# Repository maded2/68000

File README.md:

# 68000
68000 Retro computer (soon with Amiga Chipset)

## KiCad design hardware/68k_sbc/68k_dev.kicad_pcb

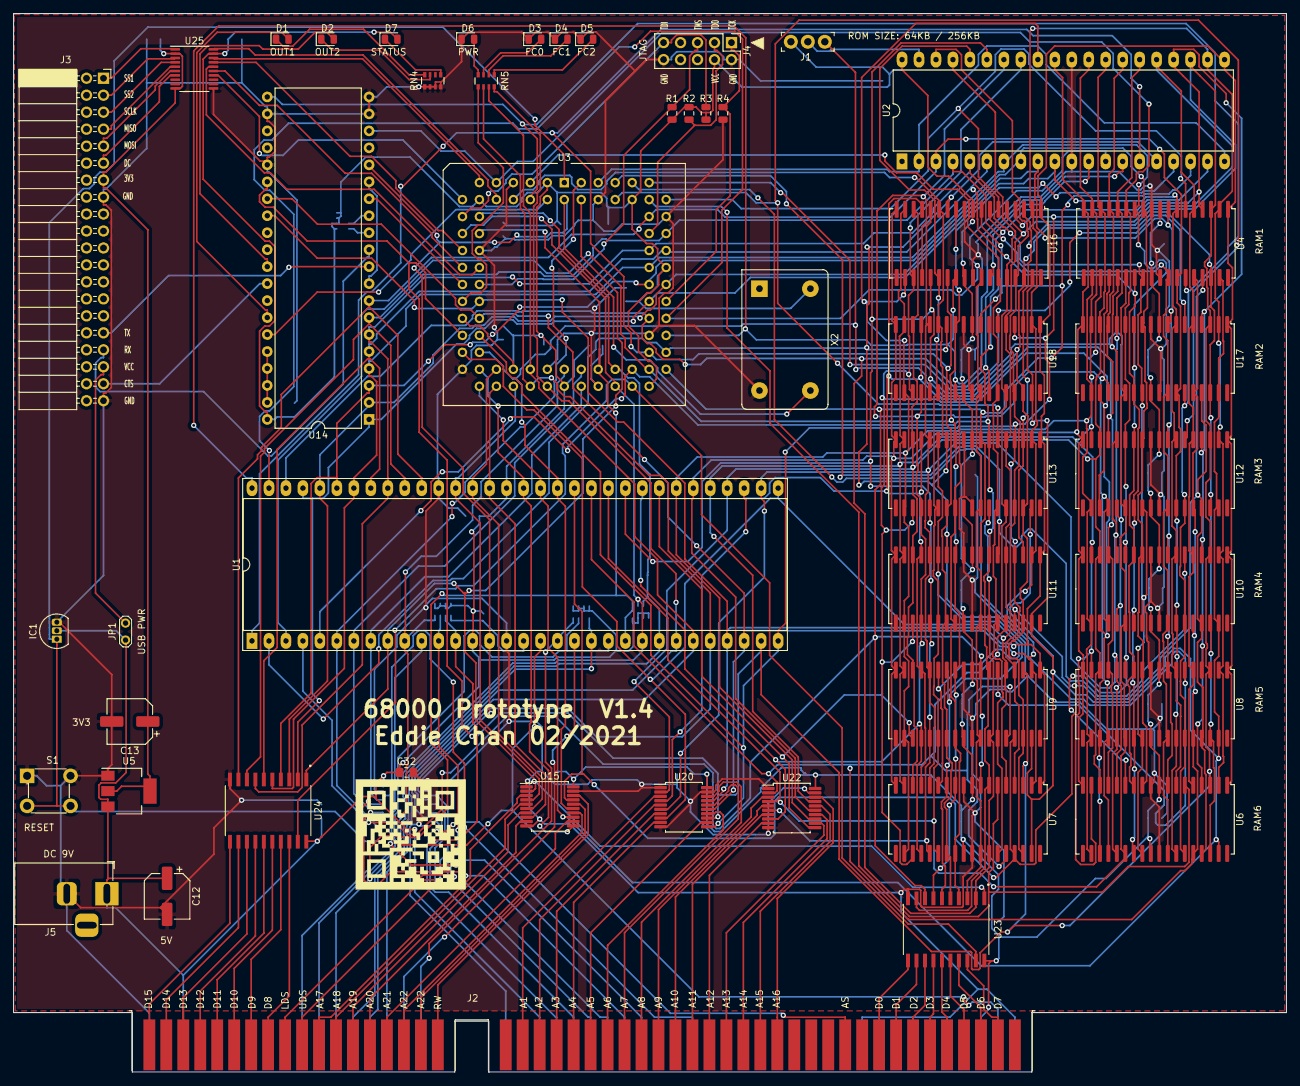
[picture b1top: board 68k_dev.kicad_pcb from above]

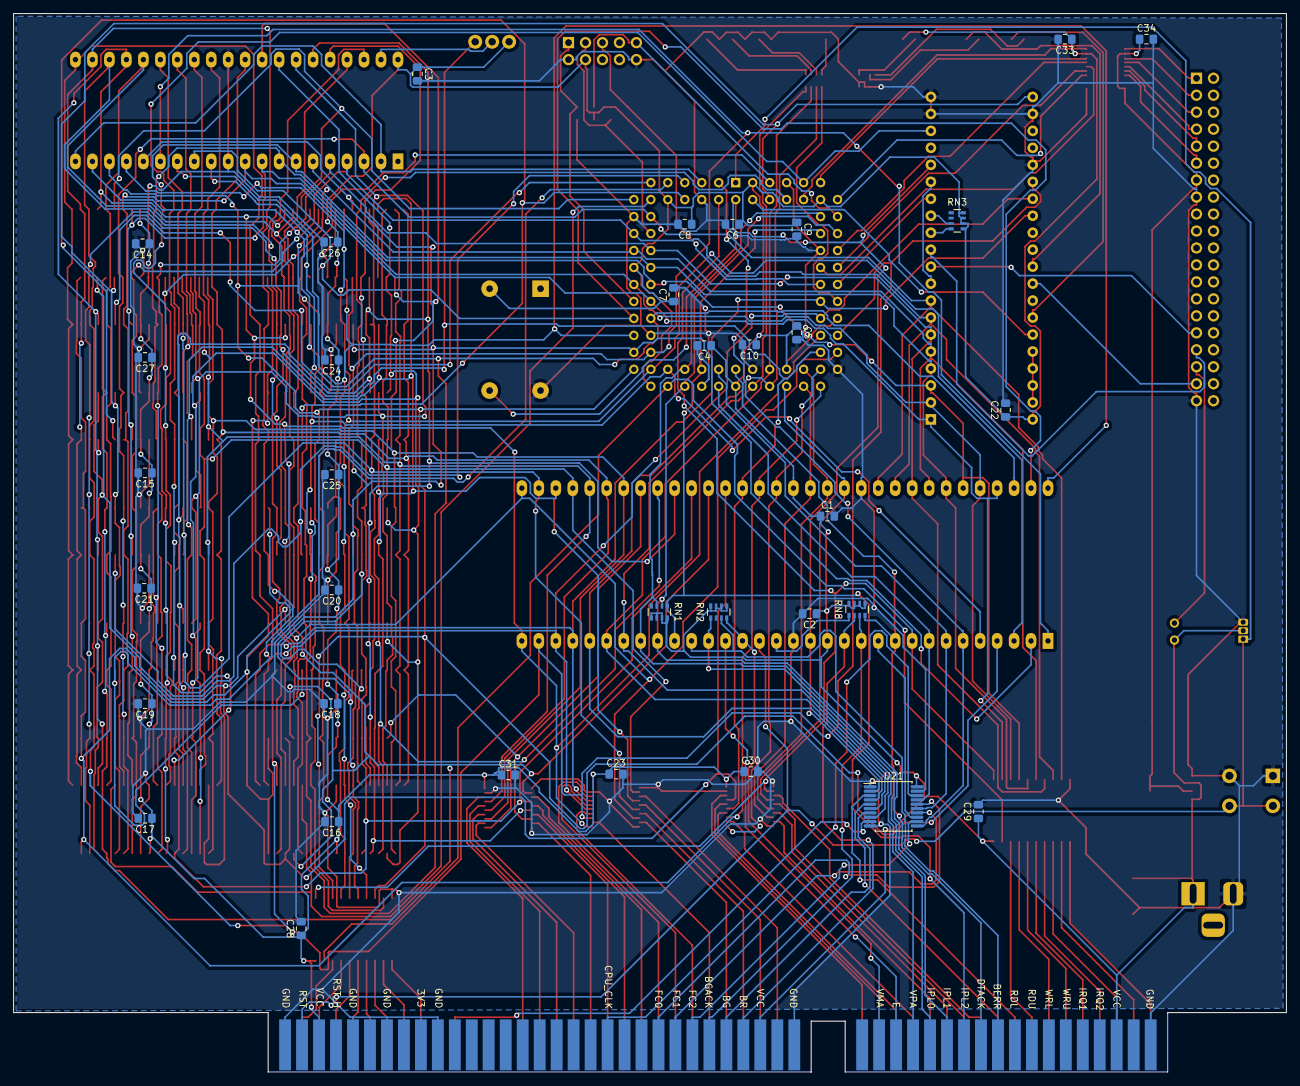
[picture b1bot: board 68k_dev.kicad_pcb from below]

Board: 2 copper layers, 190.5 x 158.4 mm, 83 parts (35 on the bottom side), 160 nets.

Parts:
C1, C2, C3, C7, C8, C9, C10, C14, C15, C16, C17, C18, C19, C20, C21, C22, C23, C24, C25, C26, C27, C28, C29, C30, C31, C32, C33, C34: 100nF; C_0805_2012Metric_Pad1.15x1.40mm_HandSolder
C4, C5, C6: 1uF; C_0805_2012Metric_Pad1.15x1.40mm_HandSolder
C12, C13: 22uF; CP_Elec_6.3x7.7
D1, D2, D3, D4, D5, D6, D7: LED; LED_0805_2012Metric
IC1: DS1813-10+T&R; TO-92L_Inline
J1: 640456-3; PinHeader_1x3_P2.54_Drill1.1mm
J2: Passive_Bus_ISA_16bit; BUS_AT
J3: Conn_02x20_Odd_Even; PinSocket_2x20_P2.54mm_Horizontal
J4: JTAG; PinHeader_2x05_P2.54mm_Vertical
J5: Barrel_Jack; BarrelJack_Horizontal
JP1: Jumper; TestPoint_2Pads_Pitch2.54mm_Drill0.8mm
R1, R2, R3, R4: 1K; R_0805_2012Metric
RN1, RN2, RN4, RN5, RN8: 470; R_Array_Convex_4x0603
RN3: 10K; R_Array_Convex_4x0603
S1: 1825910-6; Switch_Tactile_THT_6x6mm
U1: 68000D; DIP-64_W22.86mm_Socket_LongPads
U2: M27C1024; DIP-40_W15.24mm_LongPads
U3: EPM7128SLC84-15N; PLCC-84_THT-Socket
U4, U6, U7, U8, U9, U10, U11, U12, U13, U16, U17, U18: CY7C1049D; SOJ-36_10.16x23.49mm_P1.27mm_sram
U5: AMS1117-3.3; SOT-223-3_TabPin2
U14: 16550; DIP-40_W15.24mm
U15, U20, U21, U22: 74LS244; SSOP-20_5.3x7.2mm_P0.65mm
U23, U24: SN74LVC245AN; SOIC127P1032X265-20N
U25: TXS0108EPW; TSSOP-20_4.4x6.5mm_P0.65mm
X2: CXO_DIP14; Oscillator_DIP-14_LargePads

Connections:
+3V3: C13.1, C34.1, J3.13, U5.2, U25.2, U25.10
A1: U1.29, U2.21, U3.25, U4.1, U6.1, U7.1, U8.1, U9.1, U10.1, U11.1, U12.1, U13.1, U14.28, U16.1, U17.1, U18.1, U20.17
A2: U1.30, U2.22, U3.27, U4.2, U6.2, U7.2, U8.2, U9.2, U10.2, U11.2, U12.2, U13.2, U14.27, U16.2, U17.2, U18.2, U20.15
A3: U1.31, U2.23, U3.28, U4.3, U6.3, U7.3, U8.3, U9.3, U10.3, U11.3, U12.3, U13.3, U14.26, U16.3, U17.3, U18.3, U20.13
A4: U1.32, U2.24, U3.29, U4.4, U6.4, U7.4, U8.4, U9.4, U10.4, U11.4, U12.4, U13.4, U16.4, U17.4, U18.4, U20.11
A5: U1.33, U2.25, U3.30, U4.5, U6.5, U7.5, U8.5, U9.5, U10.5, U11.5, U12.5, U13.5, U16.5, U17.5, U18.5, U20.8
A6: U1.34, U2.26, U4.14, U6.14, U7.14, U8.14, U9.14, U10.14, U11.14, U12.14, U13.14, U16.14, U17.14, U18.14, U20.6
A7: U1.35, U2.27, U4.15, U6.15, U7.15, U8.15, U9.15, U10.15, U11.15, U12.15, U13.15, U16.15, U17.15, U18.15, U20.4
A8: U1.36, U2.28, U4.16, U6.16, U7.16, U8.16, U9.16, U10.16, U11.16, U12.16, U13.16, U16.16, U17.16, U18.16, U20.2
A9: U1.37, U2.29, U4.17, U6.17, U7.17, U8.17, U9.17, U10.17, U11.17, U12.17, U13.17, U16.17, U17.17, U18.17, U22.17
A10: U1.38, U2.31, U4.18, U6.18, U7.18, U8.18, U9.18, U10.18, U11.18, U12.18, U13.18, U16.18, U17.18, U18.18, U22.15
A11: U1.39, U2.32, U4.20, U6.20, U7.20, U8.20, U9.20, U10.20, U11.20, U12.20, U13.20, U16.20, U17.20, U18.20, U22.13
A12: U1.40, U2.33, U4.21, U6.21, U7.21, U8.21, U9.21, U10.21, U11.21, U12.21, U13.21, U16.21, U17.21, U18.21, U22.11
A13: U1.41, U2.34, U4.22, U6.22, U7.22, U8.22, U9.22, U10.22, U11.22, U12.22, U13.22, U16.22, U17.22, U18.22, U22.8
A14: U1.42, U2.35, U4.23, U6.23, U7.23, U8.23, U9.23, U10.23, U11.23, U12.23, U13.23, U16.23, U17.23, U18.23, U22.6
A15: U1.43, U2.36, U4.24, U6.24, U7.24, U8.24, U9.24, U10.24, U11.24, U12.24, U13.24, U16.24, U17.24, U18.24, U22.4
A16: U1.44, U2.37, U4.32, U6.32, U7.32, U8.32, U9.32, U10.32, U11.32, U12.32, U13.32, U16.32, U17.32, U18.32, U22.2
A17: U1.45, U2.38, U4.33, U6.33, U7.33, U8.33, U9.33, U10.33, U11.33, U12.33, U13.33, U15.17, U16.33, U17.33, U18.33
A18: J1.1, U1.46, U3.31, U4.34, U6.34, U7.34, U8.34, U9.34, U10.34, U11.34, U12.34, U13.34, U15.15, U16.34, U17.34, U18.34
A19: U1.47, U3.33, U4.35, U6.35, U7.35, U8.35, U9.35, U10.35, U11.35, U12.35, U13.35, U15.13, U16.35, U17.35, U18.35
A20: U1.48, U3.34, U15.11
A21: U1.50, U3.35, U15.8
A22: U1.51, U3.36, U15.6
A23: U1.52, U3.37, U15.4
AS: U1.6, U3.83, U21.11
BERR: J2.71, RN2.3, U1.22
BG: U1.11, U21.13
BGACK: J2.26, RN8.3, U1.12
BR: J2.28, RN8.2, U1.13
BUS_A1: J2.61, U20.3
BUS_A2: J2.60, U20.5
BUS_A3: J2.59, U20.7
BUS_A4: J2.58, U20.9
BUS_A5: J2.57, U20.12
BUS_A6: J2.56, U20.14
BUS_A7: J2.55, U20.16
BUS_A8: J2.54, U20.18
BUS_A9: J2.53, U22.3
BUS_A10: J2.52, U22.5
BUS_A11: J2.51, U22.7
BUS_A12: J2.50, U22.9
BUS_A13: J2.49, U22.12
BUS_A14: J2.48, U22.14
BUS_A15: J2.47, U22.16
BUS_A16: J2.46, U22.18
BUS_A17: J2.88, U15.3
BUS_A18: J2.87, U15.5
BUS_A19: J2.86, U15.7
BUS_A20: J2.85, U15.9
BUS_A21: J2.84, U15.12
BUS_A22: J2.83, U15.14
BUS_A23: J2.82, U15.16
BUS_AS: J2.42, U21.9
BUS_BG: J2.27, U21.7
BUS_CPU_CLK: J2.20, U21.18
BUS_D0: J2.40, U23.11
BUS_D1: J2.39, U23.12
BUS_D2: J2.38, U23.13
BUS_D3: J2.37, U23.14
BUS_D4: J2.36, U23.15
BUS_D5: J2.35, U23.16
BUS_D6: J2.34, U23.17
BUS_D7: J2.33, U23.18
BUS_D8: J2.91, U24.18
BUS_D9: J2.92, U24.17
BUS_D10: J2.93, U24.16
BUS_D11: J2.94, U24.15
BUS_D12: J2.95, U24.14
BUS_D13: J2.96, U24.13
BUS_D14: J2.97, U24.12
BUS_D15: J2.98, U24.11
BUS_DIR_CTRL: U3.51, U23.19, U24.19
BUS_FC0: J2.23, U21.16
BUS_FC1: J2.24, U21.14
BUS_FC2: J2.25, U21.12
BUS_LDS: J2.90, U21.3
BUS_RW: J2.81, U15.18
BUS_UDS: J2.89, U21.5
CPU_CLK: U1.15, U3.2, U14.16, U21.2, X2.8
CTS: J3.37, U14.32
D0: U1.5, U2.19, U3.52, U7.7, U9.7, U11.7, U13.7, U16.7, U18.7, U23.9
D1: U1.4, U2.18, U3.54, U7.8, U9.8, U11.8, U13.8, U16.8, U18.8, U23.8
D2: U1.3, U2.17, U3.55, U7.11, U9.11, U11.11, U13.11, U16.11, U18.11, U23.7
D3: U1.2, U2.16, U3.56, U7.12, U9.12, U11.12, U13.12, U16.12, U18.12, U23.6
D4: U1.1, U2.15, U3.57, U7.25, U9.25, U11.25, U13.25, U16.25, U18.25, U23.5
D5: U1.64, U2.14, U3.58, U7.26, U9.26, U11.26, U13.26, U16.26, U18.26, U23.4
D6: U1.63, U2.13, U3.60, U7.29, U9.29, U11.29, U13.29, U16.29, U18.29, U23.3
D7: U1.62, U2.12, U3.61, U7.30, U9.30, U11.30, U13.30, U16.30, U18.30, U23.2
D8: U1.61, U2.10, U3.63, U4.7, U6.7, U8.7, U10.7, U12.7, U14.1, U17.7, U24.2
D9: U1.60, U2.9, U3.64, U4.8, U6.8, U8.8, U10.8, U12.8, U14.2, U17.8, U24.3
D10: U1.59, U2.8, U3.65, U4.11, U6.11, U8.11, U10.11, U12.11, U14.3, U17.11, U24.4
D11: U1.58, U2.7, U3.67, U4.12, U6.12, U8.12, U10.12, U12.12, U14.4, U17.12, U24.5
D12: U1.57, U2.6, U3.68, U4.25, U6.25, U8.25, U10.25, U12.25, U14.5, U17.25, U24.6
D13: U1.56, U2.5, U3.69, U4.26, U6.26, U8.26, U10.26, U12.26, U14.6, U17.26, U24.7
D14: U1.55, U2.4, U3.70, U4.29, U6.29, U8.29, U10.29, U12.29, U14.7, U17.29, U24.8
D15: U1.54, U2.3, U3.73, U4.30, U6.30, U8.30, U10.30, U12.30, U14.8, U17.30, U24.9
DC: U3.12, U25.14
DTACK: J2.70, RN8.4, U1.10, U3.44
E: J2.65, U1.20
FC0: RN5.6, U1.28, U3.39, U21.4
FC1: RN5.7, U1.27, U3.40, U21.6
FC2: RN5.8, U1.26, U3.41, U21.8
GND: C1.2, C2.2, C3.2, C4.2, C5.2, C6.2, C7.2, C8.2, C9.2, C10.2, C12.2, C13.2, C14.2, C15.2, C16.2, C17.2, C18.2, C19.2, C20.2, C21.2, C22.2, C23.2, C24.2, C25.2, C26.2, C27.2, C28.2, C29.2, C30.2, C31.2, C32.2, C33.2, C34.2, D3.1, D4.1, D5.1, D6.1, IC1.3, J2.1, J2.5, J2.7, J2.10, J2.31, J2.80, J3.15, J3.39, J4.2, J4.10, J5.2, R4.2, RN4.1, RN4.2, RN4.3, RN4.4, S1.1, S1.2, U1.16, U1.53, U2.11, U2.30, U3.7, U3.19, U3.32, U3.42, U3.47, U3.59, U3.72, U3.82, U4.10, U4.28, U5.1, U6.10, U6.28, U7.10, U7.28, U8.10, U8.28, U9.10, U9.28, U10.10, U10.28, U11.10, U11.28, U12.10, U12.28, U13.10, U13.28, U14.19, U14.20, U14.22, U14.25, U15.1, U15.10, U15.19, U16.10, U16.28, U17.10, U17.28, U18.10, U18.28, U20.1, U20.10, U20.19, U21.1, U21.10, U21.19, U22.1, U22.10, U22.19, U23.10, U24.10, U25.11, X2.7
IO_SEL1: U3.22, U14.14
IPL0: J2.67, RN1.3, U1.25, U3.15, U3.50
IPL1: J2.68, RN1.2, U1.24, U3.16, U3.49
IPL2: J2.69, RN1.1, U1.23, U3.17, U3.48
LDS: U1.8, U3.45, U21.17
MISO: U3.21, U25.16
MOSI: U3.20, U25.15
unnamed: D1.1, RN4.8
unnamed: D1.2, U14.34
unnamed: D2.1, RN4.7
unnamed: D2.2, U14.31
unnamed: D3.2, RN5.3
unnamed: D4.2, RN5.2
unnamed: D5.2, RN5.1
unnamed: D6.2, RN5.4
unnamed: D7.1, RN4.5
unnamed: J1.2, U2.39
unnamed: J3.1, U25.1
unnamed: J3.3, U25.3
unnamed: J3.5, U25.4
unnamed: J3.7, U25.5
unnamed: J3.9, U25.6
unnamed: J3.11, U25.7
unnamed: J3.35, JP1.2
unnamed: RN3.3, U14.13
unnamed: RN3.4, U14.12
unnamed: RN8.1, U1.17
unnamed: U14.9, U14.15
unnamed: U14.36, U14.37, U14.38, U14.39
RAM1_SEL: U3.76, U6.6, U7.6
RAM2_SEL: U3.77, U8.6, U9.6
RAM3_SEL: U3.79, U10.6, U11.6
RAM4_SEL: U3.80, U12.6, U13.6
RAM5_SEL: U3.74, U4.6, U16.6
RAM6_SEL: U3.75, U17.6, U18.6
RDL: U3.5, U7.31, U9.31, U11.31, U13.31, U16.31, U18.31
RDU: U3.6, U4.31, U6.31, U8.31, U10.31, U12.31, U14.21, U17.31
ROM_SEL: U2.2, U2.20, U3.81
RST: IC1.1, J2.2, S1.3, S1.4, U1.18, U3.1
RST_H: U3.4, U14.35
RW: U1.9, U3.84, U15.2, U23.1, U24.1
RX: J3.33, U14.11
SCLK: U3.18, U25.17
SS1: U3.10, U25.20
SS2: U3.11, U25.18
STATUS: RN5.5, U3.24
TCK: J4.1, R4.1, U3.62
TDI: J4.9, R3.2, U3.14
TDO: J4.3, R2.2, U3.71
TMS: J4.5, R1.2, U3.23
TX: J3.31, U14.10
UDS: U1.7, U3.46, U21.15
VCC: C1.1, C2.1, C3.1, C4.1, C5.1, C6.1, C7.1, C8.1, C9.1, C10.1, C12.1, C14.1, C15.1, C16.1, C17.1, C18.1, C19.1, C20.1, C21.1, C22.1, C23.1, C24.1, C25.1, C26.1, C27.1, C28.1, C29.1, C30.1, C31.1, C32.1, C33.1, D7.2, IC1.2, J1.3, J2.3, J2.29, J2.78, J4.4, J5.1, JP1.1, R1.1, R2.1, R3.1, RN1.5, RN1.6, RN1.7, RN1.8, RN2.5, RN2.6, RN2.7, RN2.8, RN3.5, RN3.6, RN3.7, RN3.8, RN8.5, RN8.6, RN8.7, RN8.8, U1.14, U1.49, U2.40, U3.3, U3.13, U3.26, U3.38, U3.43, U3.53, U3.66, U3.78, U4.9, U4.27, U5.3, U6.9, U6.27, U7.9, U7.27, U8.9, U8.27, U9.9, U9.27, U10.9, U10.27, U11.9, U11.27, U12.9, U12.27, U13.9, U13.27, U14.40, U15.20, U16.9, U16.27, U17.9, U17.27, U18.9, U18.27, U20.20, U21.20, U22.20, U23.20, U24.20, U25.19, X2.14
VMA: J2.64, RN2.4, U1.19
VPA: J2.66, RN2.1, U1.21
WRL: U3.8, U7.13, U9.13, U11.13, U13.13, U16.13, U18.13
WRU: U3.9, U4.13, U6.13, U8.13, U10.13, U12.13, U14.18, U17.13

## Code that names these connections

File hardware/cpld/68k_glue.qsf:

# -------------------------------------------------------------------------- #
#
# Copyright (C) 1991-2013 Altera Corporation
# Your use of Altera Corporation's design tools, logic functions 
# and other software and tools, and its AMPP partner logic 
# functions, and any output files from any of the foregoing 
# (including device programming or simulation files), and any 
# associated documentation or information are expressly subject 
# to the terms and conditions of the Altera Program License 
# Subscription Agreement, Altera MegaCore Function License 
# Agreement, or other applicable license agreement, including, 
# without limitation, that your use is for the sole purpose of 
# programming logic devices manufactured by Altera and sold by 
# Altera or its authorized distributors.  Please refer to the 
# applicable agreement for further details.
#
# -------------------------------------------------------------------------- #
#
# Quartus II 64-Bit
# Version 13.0.1 Build 232 06/12/2013 Service Pack 1 SJ Web Edition
# Date created = 21:42:39  November 19, 2020
#
# -------------------------------------------------------------------------- #
#
# Notes:
#
# 1) The default values for assignments are stored in the file:
#		68k_glue_assignment_defaults.qdf
#    If this file doesn't exist, see file:
#		assignment_defaults.qdf
#
# 2) Altera recommends that you do not modify this file. This
#    file is updated automatically by the Quartus II software
#    and any changes you make may be lost or overwritten.
#
# -------------------------------------------------------------------------- #


set_global_assignment -name FAMILY MAX7000S
set_global_assignment -name DEVICE "EPM7128SLC84-15"
set_global_assignment -name TOP_LEVEL_ENTITY glue
set_global_assignment -name ORIGINAL_QUARTUS_VERSION "13.0 SP1"
set_global_assignment -name PROJECT_CREATION_TIME_DATE "21:42:39  NOVEMBER 19, 2020"
set_global_assignment -name LAST_QUARTUS_VERSION "13.0 SP1"
set_global_assignment -name PROJECT_OUTPUT_DIRECTORY output_files
set_global_assignment -name DEVICE_FILTER_PACKAGE PLCC
set_global_assignment -name DEVICE_FILTER_PIN_COUNT 84
set_global_assignment -name DEVICE_FILTER_SPEED_GRADE 15
set_global_assignment -name ERROR_CHECK_FREQUENCY_DIVISOR "-1"
set_global_assignment -name EDA_SIMULATION_TOOL "ModelSim-Altera (Verilog)"
set_global_assignment -name EDA_OUTPUT_DATA_FORMAT "VERILOG HDL" -section_id eda_simulation
set_global_assignment -name VERILOG_FILE 68k_glue.v
set_global_assignment -name OPTIMIZE_HOLD_TIMING OFF
set_global_assignment -name OPTIMIZE_MULTI_CORNER_TIMING OFF
set_global_assignment -name FITTER_EFFORT "STANDARD FIT"
set_global_assignment -name MAX7000_DEVICE_IO_STANDARD TTL
set_location_assignment PIN_2 -to clk
set_location_assignment PIN_83 -to as
set_location_assignment PIN_25 -to addr[1]
set_location_assignment PIN_27 -to addr[2]
set_location_assignment PIN_28 -to addr[3]
set_location_assignment PIN_29 -to addr[4]
set_location_assignment PIN_30 -to addr[5]
set_location_assignment PIN_31 -to addr[6]
set_location_assignment PIN_33 -to addr[7]
set_location_assignment PIN_34 -to addr[8]
set_location_assignment PIN_35 -to addr[9]
set_location_assignment PIN_36 -to addr[10]
set_location_assignment PIN_37 -to addr[11]
set_location_assignment PIN_48 -to addr[12]
set_location_assignment PIN_49 -to addr[13]
set_location_assignment PIN_50 -to addr[14]
set_location_assignment PIN_51 -to addr[15]
set_location_assignment PIN_52 -to addr[16]
set_location_assignment PIN_54 -to addr[17]
set_location_assignment PIN_55 -to addr[18]
set_location_assignment PIN_56 -to addr[19]
set_location_assignment PIN_57 -to addr[20]
set_location_assignment PIN_58 -to addr[21]
set_location_assignment PIN_60 -to addr[22]
set_location_assignment PIN_61 -to addr[23]
set_location_assignment PIN_45 -to lds
set_location_assignment PIN_46 -to uds
set_location_assignment PIN_5 -to rdl
set_location_assignment PIN_6 -to rdu
set_location_assignment PIN_8 -to wrl
set_location_assignment PIN_9 -to wru
set_location_assignment PIN_63 -to data[0]
set_location_assignment PIN_64 -to data[1]
set_location_assignment PIN_65 -to data[2]
set_location_assignment PIN_67 -to data[3]
set_location_assignment PIN_68 -to data[4]
set_location_assignment PIN_69 -to data[5]
set_location_assignment PIN_70 -to data[6]
set_location_assignment PIN_73 -to data[7]
set_location_assignment PIN_81 -to rom_sel
set_location_assignment PIN_80 -to ram4_sel
set_location_assignment PIN_79 -to ram3_sel
set_location_assignment PIN_77 -to ram2_sel
set_location_assignment PIN_76 -to ram1_sel
set_location_assignment PIN_75 -to io2_sel
set_location_assignment PIN_74 -to io1_sel
set_location_assignment PIN_39 -to fc[0]
set_location_assignment PIN_40 -to fc[1]
set_location_assignment PIN_41 -to fc[2]
set_location_assignment PIN_44 -to dtack
set_location_assignment PIN_71 -to TDO
set_location_assignment PIN_14 -to TDI
set_location_assignment PIN_62 -to TCK
set_location_assignment PIN_23 -to TMS
set_location_assignment PIN_1 -to rst
set_location_assignment PIN_4 -to rst_h
set_location_assignment PIN_84 -to rw
set_location_assignment PIN_15 -to ipl[0]
set_location_assignment PIN_16 -to ipl[1]
set_location_assignment PIN_17 -to ipl[2]
set_location_assignment PIN_22 -to irq1
set_location_assignment PIN_24 -to irq2
set_location_assignment PIN_18 -to sclk
set_location_assignment PIN_20 -to mosi
set_location_assignment PIN_21 -to miso
set_location_assignment PIN_10 -to ss1
set_location_assignment PIN_11 -to ss2
set_instance_assignment -name GLOBAL_SIGNAL GLOBAL_CLOCK -to clk
set_instance_assignment -name GLOBAL_SIGNAL "GLOBAL CLOCK" -to as
set_instance_assignment -name GLOBAL_SIGNAL OFF -to rst
set_instance_assignment -name GLOBAL_SIGNAL OFF -to rw
set_location_assignment PIN_12 -to dc
set_global_assignment -name VERILOG_FILE SPI_Master.v
set_instance_assignment -name FAST_INPUT_REGISTER ON -to as
set_instance_assignment -name FAST_INPUT_REGISTER ON -to clk
set_global_assignment -name MAX7000_OPTIMIZATION_TECHNIQUE AREA
set_global_assignment -name SYNTH_TIMING_DRIVEN_SYNTHESIS OFF
set_global_assignment -name SIGNALTAP_FILE stp1.stp

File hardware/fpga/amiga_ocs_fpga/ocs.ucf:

//global system clock
NET "sys_clk" LOC = A10 | IOSTANDARD = LVTTL;
//reset signal
NET "rst" 	LOC = T8 	| IOSTANDARD = LVTTL;
//led_1 signal
NET "led_1" LOC = T9 | IOSTANDARD = LVTTL;
//led_2 signal
NET "led_2" LOC = R9 | IOSTANDARD = LVTTL;

// U8
#NET "data<0>"      LOC = A14   | IOSTANDARD = LVTTL;
#NET "data<1>"      LOC = C13   | IOSTANDARD = LVTTL;
#NET "data<2>"      LOC = B12   | IOSTANDARD = LVTTL;
#NET "data<3>"      LOC = C11   | IOSTANDARD = LVTTL;
#NET "data<4>"      LOC = B10   | IOSTANDARD = LVTTL;
#NET "data<5>"      LOC = C9    | IOSTANDARD = LVTTL;
#NET "data<6>"      LOC = B8    | IOSTANDARD = LVTTL;
#NET "data<7>"      LOC = C7    | IOSTANDARD = LVTTL;
#NET "data<8>"      LOC = B6    | IOSTANDARD = LVTTL;
#NET "data<9>"      LOC = B5    | IOSTANDARD = LVTTL;
#NET "data<10>"     LOC = E10   | IOSTANDARD = LVTTL;
#NET "data<11>"     LOC = E11   | IOSTANDARD = LVTTL;
#NET "data<12>"     LOC = F9    | IOSTANDARD = LVTTL;
#NET "data<13>"     LOC = C8    | IOSTANDARD = LVTTL;
#NET "data<14>"     LOC = E7    | IOSTANDARD = LVTTL;
#NET "data<15>"     LOC = F7    | IOSTANDARD = LVTTL;
#NET "rw"        LOC = D6    | IOSTANDARD = LVTTL;
NET "cpu_clk"   LOC = M7    | IOSTANDARD = LVTTL;
#NET "rst"       LOC = N8    | IOSTANDARD = LVTTL;
#NET "lds"       LOC = P9    | IOSTANDARD = LVTTL;
#NET "uds"       LOC = T5    | IOSTANDARD = LVTTL;
#NET "dtack"     LOC = T6    | IOSTANDARD = LVTTL;3
#NET "bgack"     LOC = N9    | IOSTANDARD = LVTTL;
#NET "vma"       LOC = L8    | IOSTANDARD = LVTTL;
#NET "e"         LOC = L10   | IOSTANDARD = LVTTL;
#NET "vpa"       LOC = P12   | IOSTANDARD = LVTTL;
#NET "berr"      LOC = R9    | IOSTANDARD = LVTTL;

#NET "addr<1>"      LOC = B14   | IOSTANDARD = LVTTL;
#NET "addr<2>"      LOC = A13   | IOSTANDARD = LVTTL;
#NET "addr<3>"      LOC = A12   | IOSTANDARD = LVTTL;
#NET "addr<4>"      LOC = A11   | IOSTANDARD = LVTTL;
#NET "addr<5>"      LOC = A9    | IOSTANDARD = LVTTL;
#NET "addr<6>"      LOC = A8    | IOSTANDARD = LVTTL;
#NET "addr<7>"      LOC = A7    | IOSTANDARD = LVTTL;
#NET "addr<8>"      LOC = A6    | IOSTANDARD = LVTTL;
#NET "addr<9>"      LOC = A5    | IOSTANDARD = LVTTL;
#NET "addr<10>"     LOC = A4    | IOSTANDARD = LVTTL;
#NET "addr<11>"     LOC = C10   | IOSTANDARD = LVTTL;
#NET "addr<12>"     LOC = F10   | IOSTANDARD = LVTTL;
#NET "addr<13>"     LOC = D9    | IOSTANDARD = LVTTL;
#NET "addr<14>"     LOC = D8    | IOSTANDARD = LVTTL;
#NET "addr<15>"     LOC = E6    | IOSTANDARD = LVTTL;
#NET "addr<16>"     LOC = C6    | IOSTANDARD = LVTTL;
#NET "addr<17>"     LOC = N6    | IOSTANDARD = LVTTL;
#NET "addr<18>"     LOC = P6    | IOSTANDARD = LVTTL;
#NET "addr<19>"     LOC = L7    | IOSTANDARD = LVTTL;
#NET "addr<20>"     LOC = T4    | IOSTANDARD = LVTTL;
#NET "addr<21>"     LOC = R5    | IOSTANDARD = LVTTL;
#NET "addr<22>"     LOC = T7    | IOSTANDARD = LVTTL;
#NET "addr<23>"     LOC = M9    | IOSTANDARD = LVTTL;
NET "as"        LOC = M10   | IOSTANDARD = LVTTL;
#NET "ipl<0>"    LOC = P11   | IOSTANDARD = LVTTL;
#NET "ipl<1>"    LOC = M11   | IOSTANDARD = LVTTL;
#NET "ipl<2>"    LOC = T9    | IOSTANDARD = LVTTL;



// U7
NET "vga_vsync"    LOC = C15   | IOSTANDARD = LVTTL;
NET "vga_hsync"    LOC = D14   | IOSTANDARD = LVTTL;

NET "vga_b<0>" LOC = E15  | IOSTANDARD = LVTTL;
NET "vga_b<1>" LOC = F15  | IOSTANDARD = LVTTL;
NET "vga_b<2>" LOC = G11  | IOSTANDARD = LVTTL;
NET "vga_b<3>" LOC = F14  | IOSTANDARD = LVTTL;
NET "vga_b<4>" LOC = G16  | IOSTANDARD = LVTTL;
NET "vga_b<5>" LOC = H15  | IOSTANDARD = LVTTL;

NET "vga_g<0>" LOC = G12  | IOSTANDARD = LVTTL;
NET "vga_g<1>" LOC = H13  | IOSTANDARD = LVTTL;
NET "vga_g<2>" LOC = J14  | IOSTANDARD = LVTTL;
NET "vga_g<3>" LOC = J11  | IOSTANDARD = LVTTL;
NET "vga_g<4>" LOC = K14  | IOSTANDARD = LVTTL;
NET "vga_g<5>" LOC = K15  | IOSTANDARD = LVTTL;

NET "vga_r<0>" LOC = L16  | IOSTANDARD = LVTTL;
NET "vga_r<1>" LOC = K11  | IOSTANDARD = LVTTL;
NET "vga_r<2>" LOC = M15  | IOSTANDARD = LVTTL;
NET "vga_r<3>" LOC = N14  | IOSTANDARD = LVTTL;
NET "vga_r<4>" LOC = M13  | IOSTANDARD = LVTTL;
NET "vga_r<5>" LOC = L12  | IOSTANDARD = LVTTL;

#NET "gpio00"    LOC = E12   | IOSTANDARD = LVTTL;
#NET "gpio01"    LOC = B15   | IOSTANDARD = LVTTL;
#NET "gpio02"    LOC = C15   | IOSTANDARD = LVTTL;
#NET "gpio03"    LOC = D14   | IOSTANDARD = LVTTL;
#NET "gpio04"    LOC = E15   | IOSTANDARD = LVTTL;
#NET "gpio05"    LOC = F15   | IOSTANDARD = LVTTL;
#NET "gpio06"    LOC = G11   | IOSTANDARD = LVTTL;
#NET "gpio07"    LOC = F14   | IOSTANDARD = LVTTL;
#NET "gpio08"    LOC = G16   | IOSTANDARD = LVTTL;
#NET "gpio09"    LOC = H15   | IOSTANDARD = LVTTL;
#NET "gpio10"    LOC = G12   | IOSTANDARD = LVTTL;
#NET "gpio11"    LOC = H13   | IOSTANDARD = LVTTL;
#NET "gpio12"    LOC = J14   | IOSTANDARD = LVTTL;
#NET "gpio13"    LOC = J11   | IOSTANDARD = LVTTL;
#NET "gpio14"    LOC = K14   | IOSTANDARD = LVTTL;
#NET "gpio15"    LOC = K15   | IOSTANDARD = LVTTL;
#NET "gpio16"    LOC = L16   | IOSTANDARD = LVTTL;
#NET "gpio17"    LOC = K11   | IOSTANDARD = LVTTL;
#NET "gpio18"    LOC = M15   | IOSTANDARD = LVTTL;
#NET "gpio19"    LOC = N14   | IOSTANDARD = LVTTL;
#NET "gpio20"    LOC = M13   | IOSTANDARD = LVTTL;
#NET "gpio21"    LOC = L12   | IOSTANDARD = LVTTL;
#NET "gpio26"    LOC = P15   | IOSTANDARD = LVTTL;
#NET "gpio27"    LOC = R15   | IOSTANDARD = LVTTL;
#NET "gpio24"    LOC = R14   | IOSTANDARD = LVTTL;
#NET "gpio23"    LOC = T13   | IOSTANDARD = LVTTL;
#NET "gpio22"    LOC = T12   | IOSTANDARD = LVTTL;
#
#NET "gpio37"    LOC = E13   | IOSTANDARD = LVTTL;
#NET "gpio36"    LOC = B16   | IOSTANDARD = LVTTL;
#NET "gpio35"    LOC = C16   | IOSTANDARD = LVTTL;
#NET "gpio34"    LOC = D16   | IOSTANDARD = LVTTL;
#NET "gpio33"    LOC = E16   | IOSTANDARD = LVTTL;
#NET "gpio32"    LOC = F16   | IOSTANDARD = LVTTL;
#NET "gpio31"    LOC = F12   | IOSTANDARD = LVTTL;
#NET "gpio30"    LOC = F13   | IOSTANDARD = LVTTL;
#NET "gpio29"    LOC = G14   | IOSTANDARD = LVTTL;
#NET "gpio28"    LOC = H16   | IOSTANDARD = LVTTL;
#NET "gpio27"    LOC = H11   | IOSTANDARD = LVTTL;
#NET "gpio38"    LOC = H14   | IOSTANDARD = LVTTL;
#NET "gpio39"    LOC = J16   | IOSTANDARD = LVTTL;
#NET "gpio40"    LOC = J12   | IOSTANDARD = LVTTL;
#NET "gpio41"    LOC = J13   | IOSTANDARD = LVTTL;
#NET "gpio42"    LOC = K16   | IOSTANDARD = LVTTL;
#NET "gpio43"    LOC = L14   | IOSTANDARD = LVTTL;
#NET "gpio44"    LOC = K12   | IOSTANDARD = LVTTL;
#NET "gpio45"    LOC = M16   | IOSTANDARD = LVTTL;
#NET "gpio46"    LOC = N16   | IOSTANDARD = LVTTL;
#NET "gpio47"    LOC = M14   | IOSTANDARD = LVTTL;
#NET "gpio48"    LOC = L13   | IOSTANDARD = LVTTL;
#NET "br"        LOC = P16   | IOSTANDARD = LVTTL;
#NET "bg"        LOC = R16   | IOSTANDARD = LVTTL;
#NET "fc<0>"     LOC = T15   | IOSTANDARD = LVTTL;
#NET "fc<1>"     LOC = T14   | IOSTANDARD = LVTTL;
#NET "fc<2>"     LOC = R12   | IOSTANDARD = LVTTL;

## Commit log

2021-01-05 Initial import
2021-01-05 added readme
2021-01-05 Fixed v1.2 pcb design bug
2021-01-06 building of standalone C programs with GCC toolchain
2021-01-08 Added User Mode GCC support with soft floating point math
2021-01-09 update cpld project files
2021-01-17 added memory tester for the monitor.
    WIP SPI master for the CPLD
2021-01-23 added spi master and example
2021-01-23 added oled fonts and bitmap support
2021-01-28 updated SPI code
2021-01-31 Amiga chipset prototype addon card
2021-01-31 refactor to use baselibc and separate libsys
2021-02-06 lib refactor
